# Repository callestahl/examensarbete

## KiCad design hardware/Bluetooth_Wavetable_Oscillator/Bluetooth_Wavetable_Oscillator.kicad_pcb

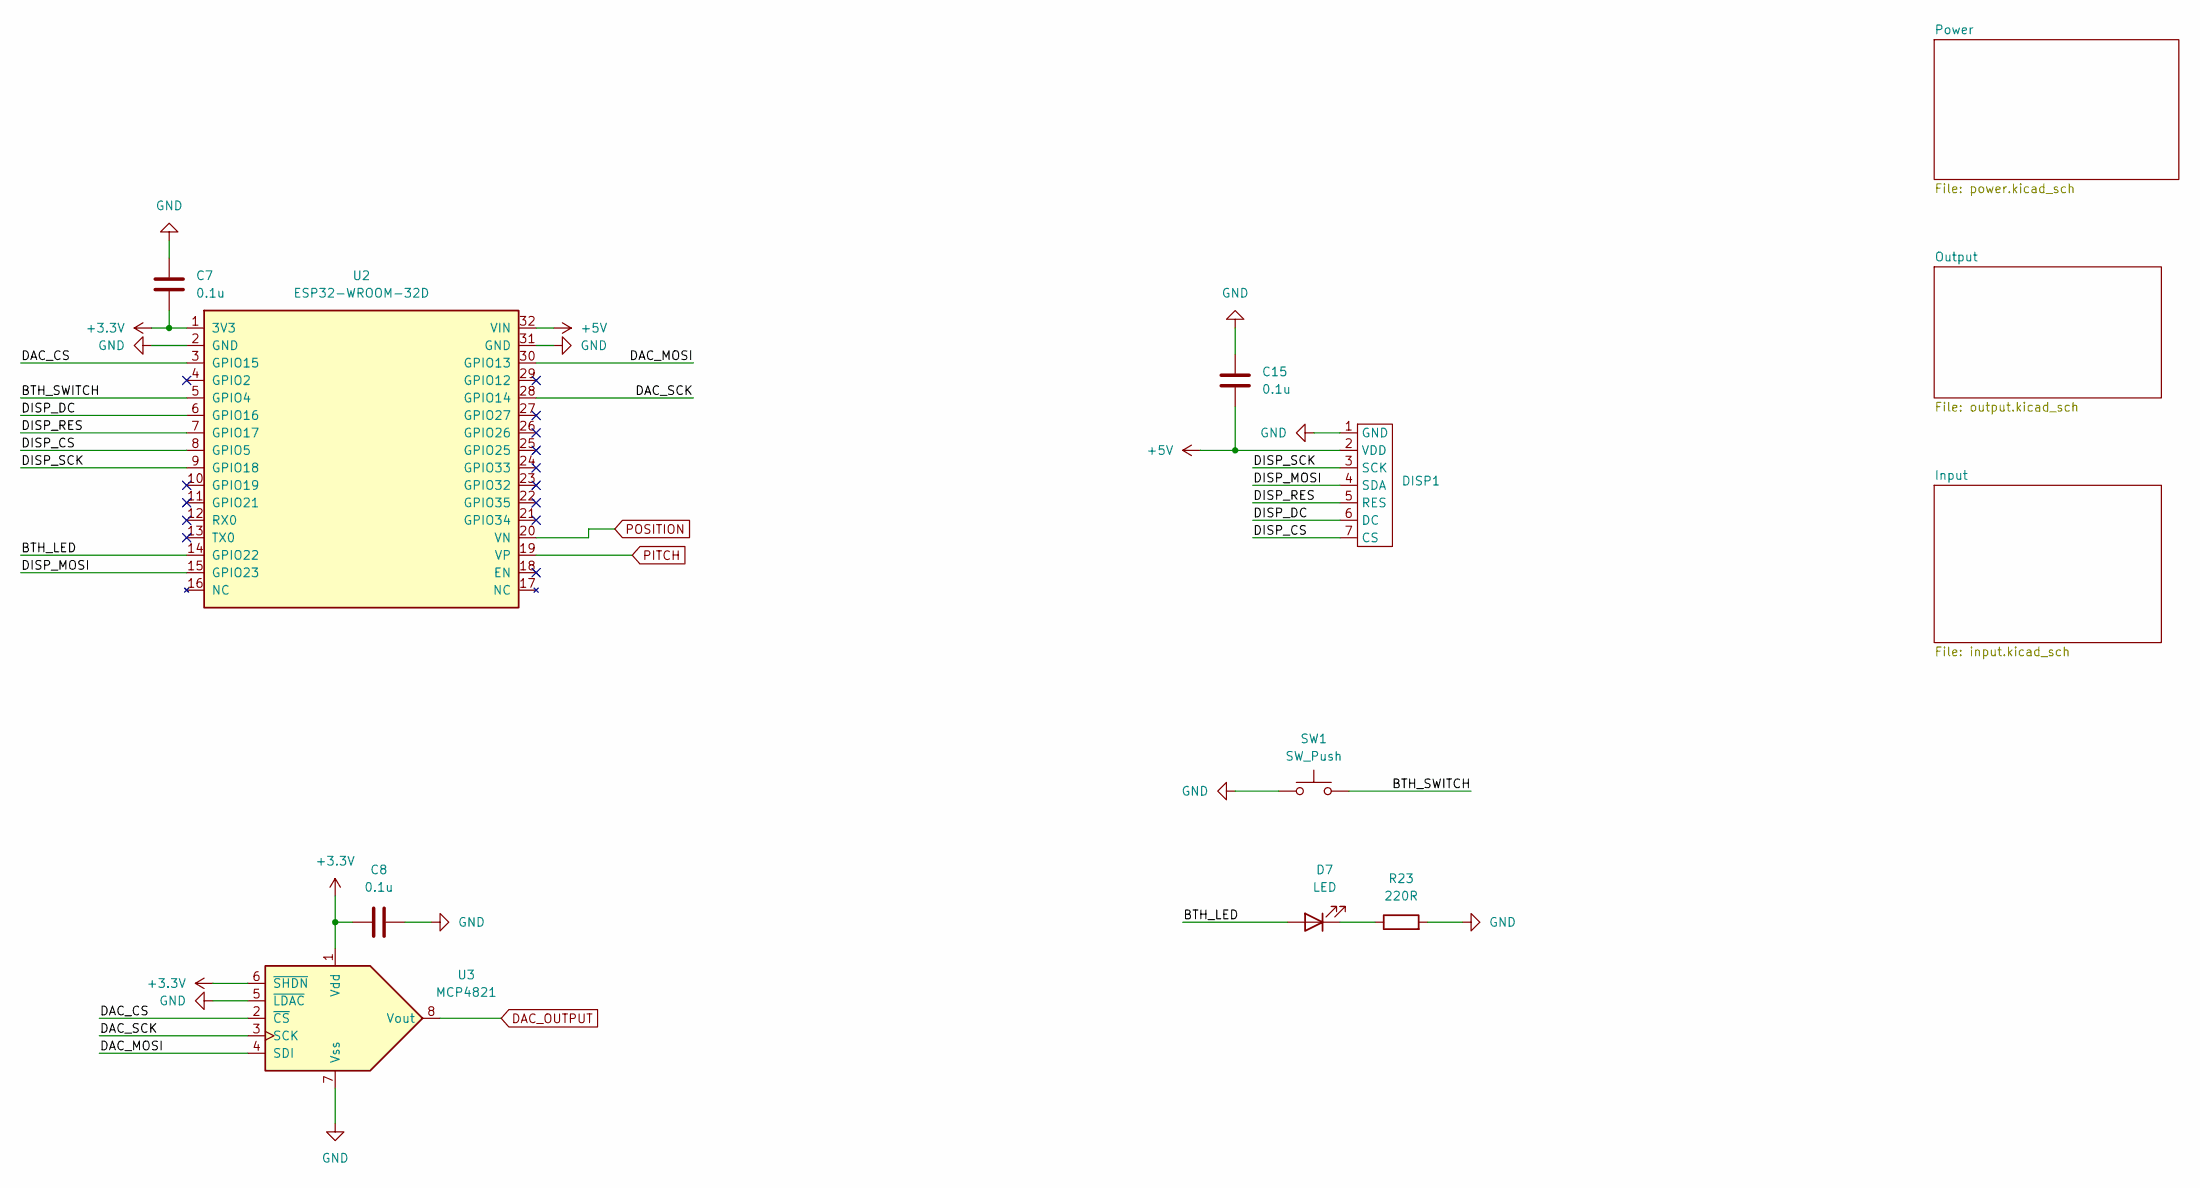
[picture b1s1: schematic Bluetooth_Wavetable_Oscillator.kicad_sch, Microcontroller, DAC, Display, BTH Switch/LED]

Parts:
C7, C8, C15: 0.1u; C_Disc_D5.0mm_W2.5mm_P5.00mm
D7: LED; D_A-405_P2.54mm_Vertical_AnodeUp
DISP1: 1.5inch_RGB_OLED_Module
R23: 220R; R_Axial_DIN0204_L3.6mm_D1.6mm_P2.54mm_Vertical
SW1: SW_Push; 6Pin-Switch-Button
U2: ESP32-WROOM-32D; ESP32
U3: MCP4821; DIP-8_W7.62mm

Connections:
+3.3V: C7.2, C8.1, U2.1 (3V3), U3.1 (Vdd), U3.6 (~SHDN); also elsewhere on the board
+5V: C15.2, DISP1.2 (VDD), U2.32 (VIN); also elsewhere on the board
/BTH_LED: D7.2 (A), U2.14 (GPIO22)
/BTH_SWITCH: SW1.2, U2.5 (GPIO4)
/DAC_CS: U2.3 (GPIO15), U3.2 (~CS)
/DAC_MOSI: U2.30 (GPIO13), U3.4 (SDI)
/DAC_SCK: U2.28 (GPIO14), U3.3 (SCK)
/DISP_CS: DISP1.7 (CS), U2.8 (GPIO5)
/DISP_DC: DISP1.6 (DC), U2.6 (GPIO16)
/DISP_MOSI: DISP1.4 (SDA), U2.15 (GPIO23)
/DISP_RES: DISP1.5 (RES), U2.7 (GPIO17)
/DISP_SCK: DISP1.3 (SCK), U2.9 (GPIO18)
DAC_OUTPUT: U3.8 (Vout); also elsewhere on the board
GND: C7.1, C8.2, C15.1, DISP1.1 (GND), R23.2, SW1.1, U2.2 (GND), U2.31 (GND), U3.5 (~LDAC), U3.7 (Vss); also elsewhere on the board
unnamed: D7.1 (K), R23.1
PITCH: U2.19 (VP); also elsewhere on the board
POSITION: U2.20 (VN); also elsewhere on the board

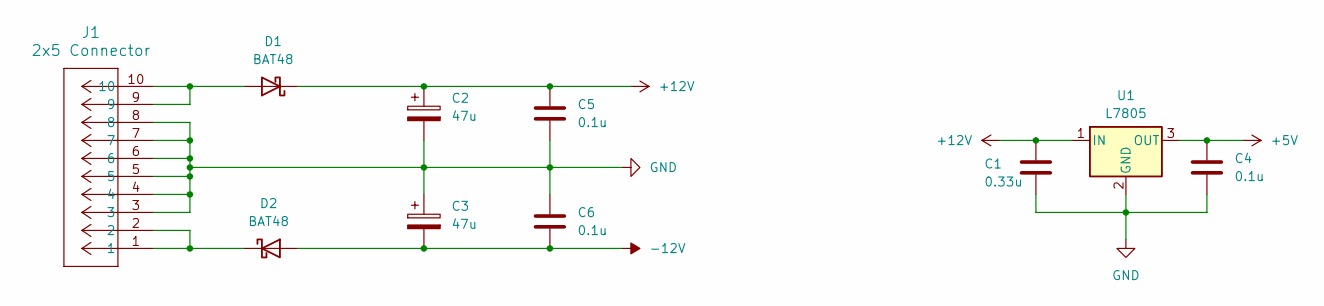
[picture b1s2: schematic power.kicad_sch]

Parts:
C1: 0.33u; C_Disc_D5.0mm_W2.5mm_P5.00mm
C2, C3: 47u; CP_Radial_D5.0mm_P2.50mm
C4, C5, C6: 0.1u; C_Disc_D5.0mm_W2.5mm_P5.00mm
D1, D2: BAT48; D_DO-35_SOD27_P2.54mm_Vertical_KathodeUp
J1: 2x5 Connector; 10_pin_eurorack_connector
U1: L7805; TO-220-3_Horizontal_TabDown

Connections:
+5V: C4.1, U1.3 (OUT); also elsewhere on the board
+12V: C1.1, C2.1, C5.1, D1.1 (K), U1.1 (IN); also elsewhere on the board
-12V: C3.2, C6.2, D2.2 (A); also elsewhere on the board
GND: C1.2, C2.2, C3.1, C4.2, C5.2, C6.1, J1.3, J1.4, J1.5, J1.6, J1.7, J1.8, U1.2 (GND); also elsewhere on the board
unnamed: D1.2 (A), J1.9, J1.10
unnamed: D2.1 (K), J1.1, J1.2

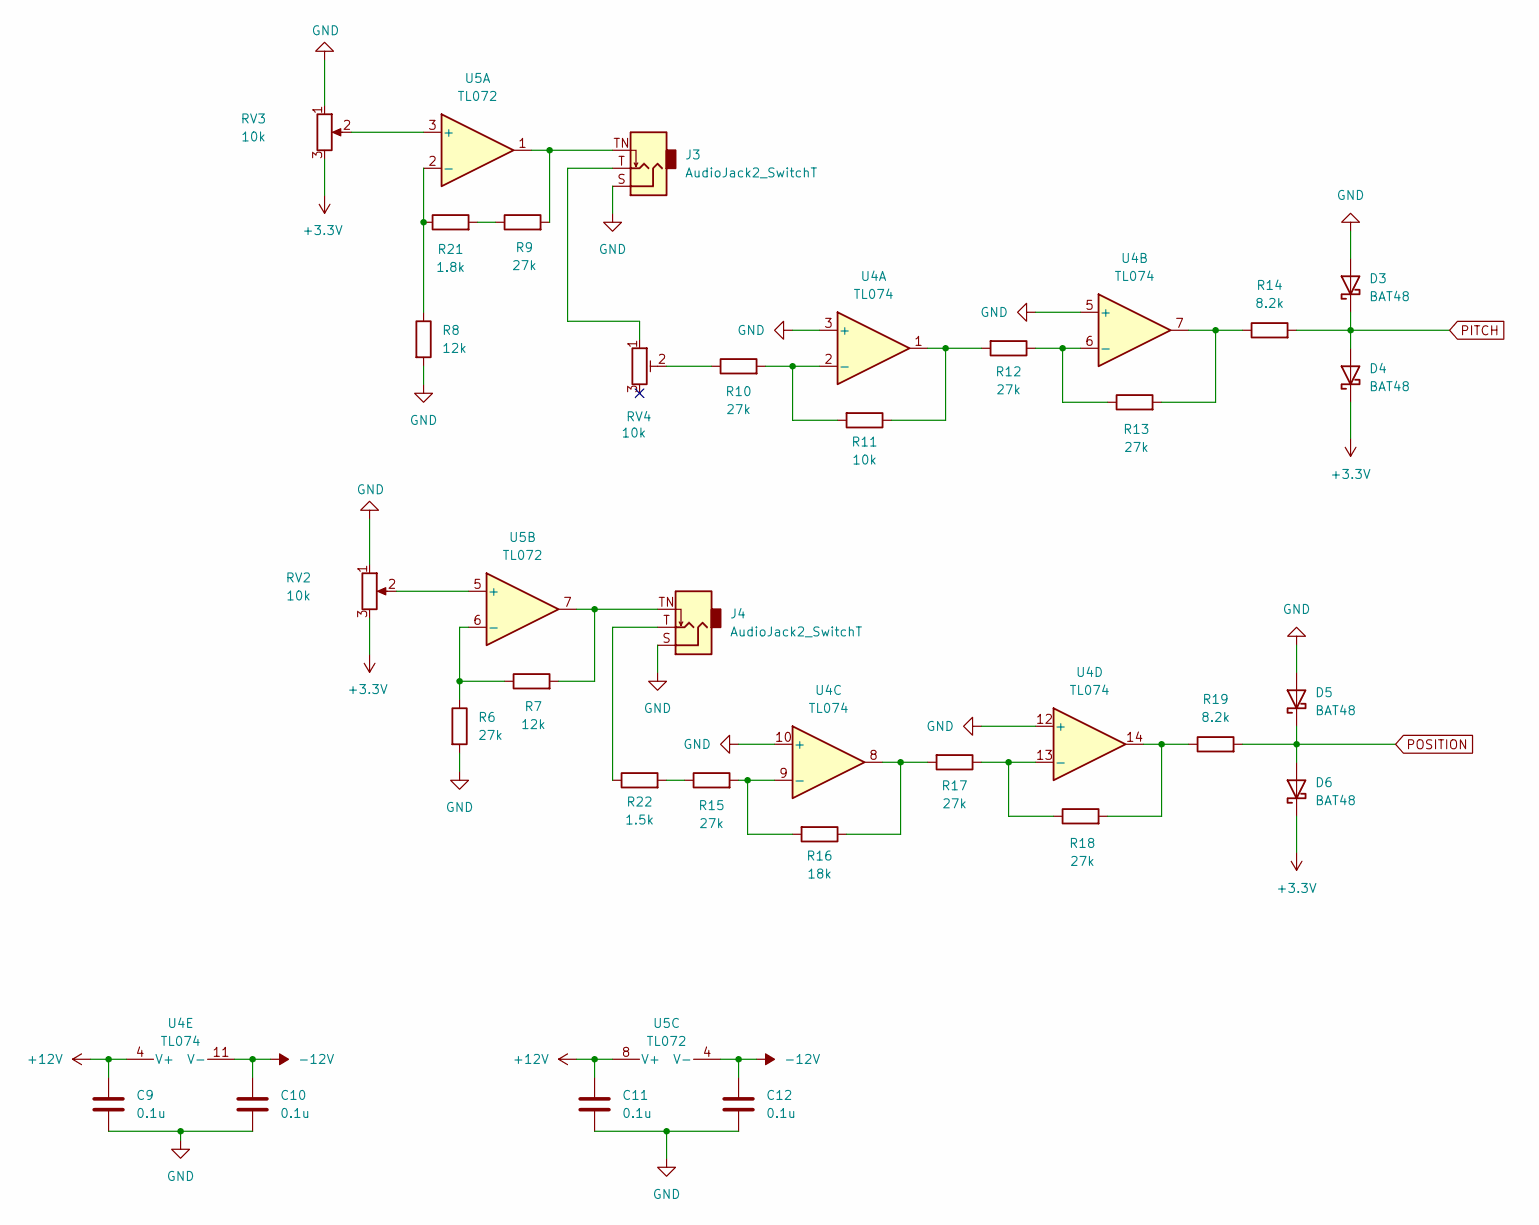
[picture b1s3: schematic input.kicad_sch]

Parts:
C9, C10, C11, C12: 0.1u; C_Disc_D5.0mm_W2.5mm_P5.00mm
D3, D4, D5, D6: BAT48; D_DO-34_SOD68_P7.62mm_Horizontal
J3, J4: AudioJack2_SwitchT; Jack_3.5mm_QingPu_WQP-PJ398SM_Vertical_CircularHoles
R6: 27k; R_Axial_DIN0204_L3.6mm_D1.6mm_P7.62mm_Horizontal
R7: 12k; R_Axial_DIN0204_L3.6mm_D1.6mm_P7.62mm_Horizontal
R8: 12k; R_Axial_DIN0204_L3.6mm_D1.6mm_P2.54mm_Vertical
R9, R10, R12, R13, R15, R17, R18: 27k; R_Axial_DIN0204_L3.6mm_D1.6mm_P2.54mm_Vertical
R11: 10k; R_Axial_DIN0204_L3.6mm_D1.6mm_P2.54mm_Vertical
R14, R19: 8.2k; R_Axial_DIN0204_L3.6mm_D1.6mm_P2.54mm_Vertical
R16: 18k; R_Axial_DIN0204_L3.6mm_D1.6mm_P2.54mm_Vertical
R21: 1.8k; R_Axial_DIN0204_L3.6mm_D1.6mm_P2.54mm_Vertical
R22: 1.5k; R_Axial_DIN0204_L3.6mm_D1.6mm_P2.54mm_Vertical
RV2, RV3: 10k; Potentiometer_Bourns_PTV09A-1_Single_Vertical
RV4: 10k; Trimmer-potentiometer
U4: TL074; DIP-14_W7.62mm
U5: TL072; DIP-8_W7.62mm

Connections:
+3.3V: D4.1 (K), D6.1 (K), RV2.3, RV3.3; also elsewhere on the board
+12V: C9.1, C11.1, U4.4 (V+), U5.8 (V+); also elsewhere on the board
-12V: C10.1, C12.1, U4.11 (V-), U5.4 (V-); also elsewhere on the board
GND: C9.2, C10.2, C11.2, C12.2, D3.2 (A), D5.2 (A), J3.S, J4.S, R6.2, R8.2, RV2.1, RV3.1, U4.3 (+), U4.5 (+), U4.10 (+), U4.12 (+); also elsewhere on the board
unnamed: J3.T, RV4.1
unnamed: J3.TN, R9.2, U5.1
unnamed: J4.T, R22.1
unnamed: J4.TN, R7.2, U5.7
unnamed: R10.1, RV4.2
unnamed: R11.1, R12.2, U4.1
unnamed: R13.2, R14.1, U4.7
unnamed: R15.1, R22.2
unnamed: R16.1, R17.2, U4.8
unnamed: R18.2, R19.1, U4.14
unnamed: R9.1, R21.2
unnamed: R10.2, R11.2, U4.2 (-)
unnamed: R12.1, R13.1, U4.6 (-)
unnamed: R15.2, R16.2, U4.9 (-)
unnamed: R17.1, R18.1, U4.13 (-)
unnamed: RV3.2, U5.3 (+)
unnamed: R8.1, R21.1, U5.2 (-)
unnamed: RV2.2, U5.5 (+)
unnamed: R6.1, R7.1, U5.6 (-)
PITCH: D3.1 (K), D4.2 (A), R14.2; also elsewhere on the board
POSITION: D5.1 (K), D6.2 (A), R19.2; also elsewhere on the board

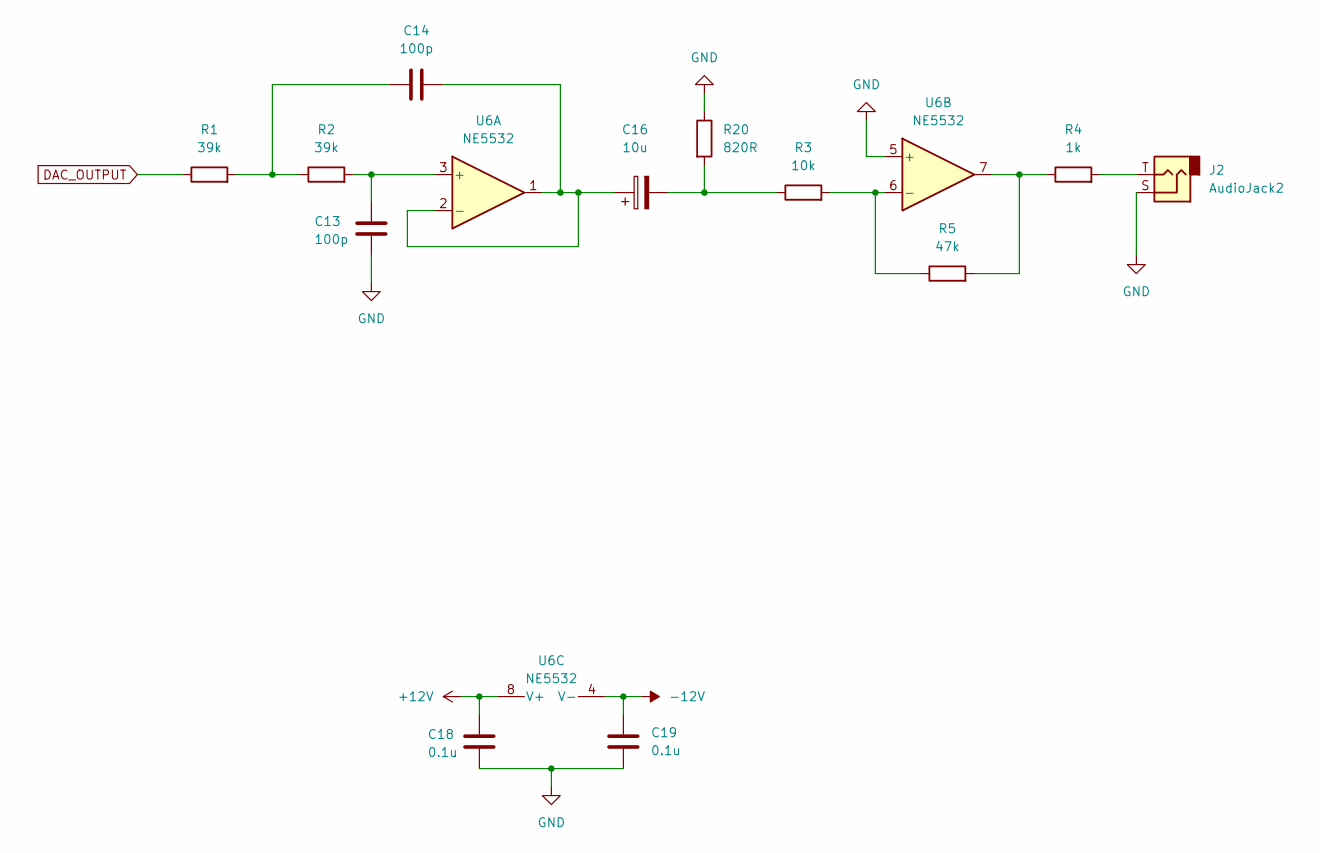
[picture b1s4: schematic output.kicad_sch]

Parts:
C13, C14: 100p; C_Disc_D5.0mm_W2.5mm_P5.00mm
C16: 10u; CP_Radial_D5.0mm_P2.50mm
C18, C19: 0.1u; C_Disc_D5.0mm_W2.5mm_P5.00mm
J2: AudioJack2; Jack_3.5mm_QingPu_WQP-PJ398SM_Vertical_CircularHoles
R1, R2: 39k; R_Axial_DIN0204_L3.6mm_D1.6mm_P7.62mm_Horizontal
R3: 10k; R_Axial_DIN0204_L3.6mm_D1.6mm_P7.62mm_Horizontal
R4: 1k; R_Axial_DIN0204_L3.6mm_D1.6mm_P7.62mm_Horizontal
R5: 47k; R_Axial_DIN0204_L3.6mm_D1.6mm_P7.62mm_Horizontal
R20: 820R; R_Axial_DIN0204_L3.6mm_D1.6mm_P7.62mm_Horizontal
U6: NE5532; DIP-8_W7.62mm

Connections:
+12V: C18.1, U6.8 (V+); also elsewhere on the board
-12V: C19.1, U6.4 (V-); also elsewhere on the board
DAC_OUTPUT: R1.1; also elsewhere on the board
GND: C13.2, C18.2, C19.2, J2.S, R20.1, U6.5 (+); also elsewhere on the board
unnamed: C14.2, R1.2, R2.1
unnamed: C16.2, R3.1, R20.2
unnamed: J2.T, R4.2
unnamed: R4.1, R5.2, U6.7
unnamed: C13.1, R2.2, U6.3 (+)
unnamed: C14.1, C16.1, U6.1, U6.2 (-)
unnamed: R3.2, R5.1, U6.6 (-)

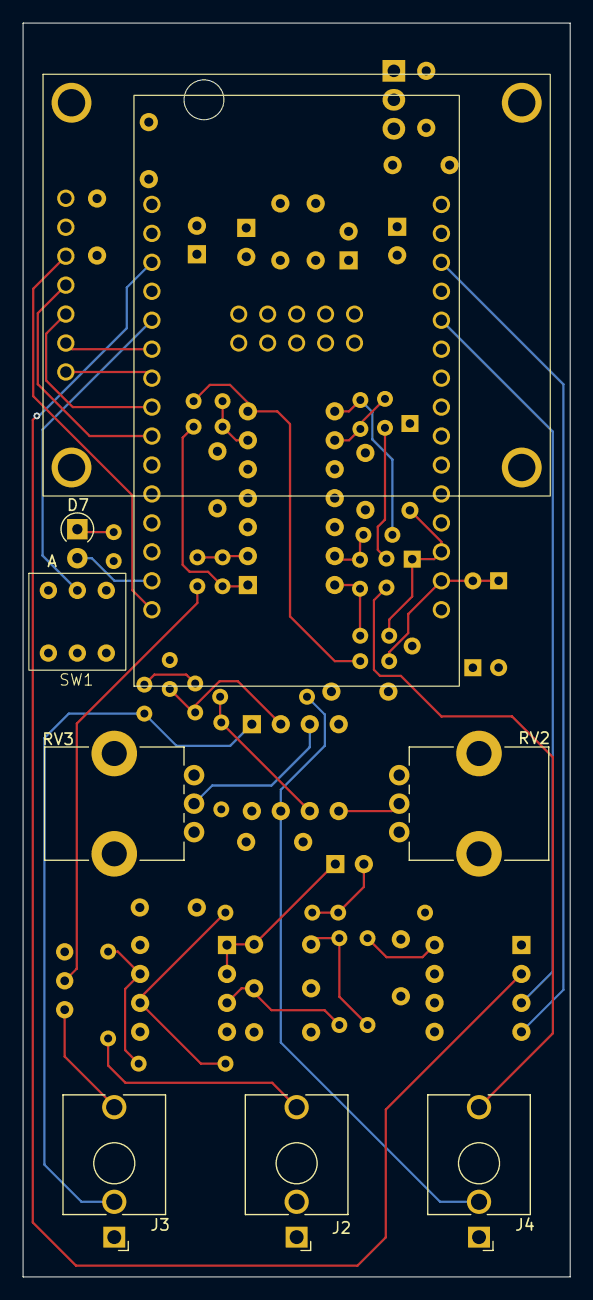
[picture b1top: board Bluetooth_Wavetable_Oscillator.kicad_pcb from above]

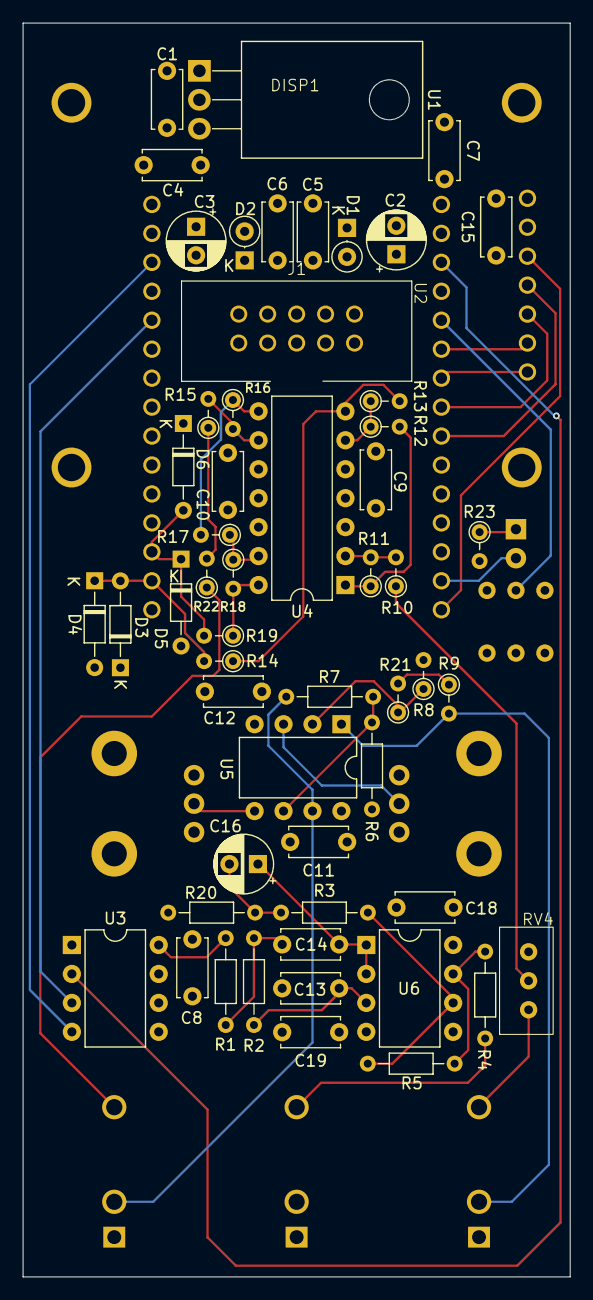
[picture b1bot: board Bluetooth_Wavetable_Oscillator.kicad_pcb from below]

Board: 4 copper layers, 48.0 x 110.0 mm, 63 parts (54 on the bottom side), 47 nets.

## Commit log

2024-11-06 first
2024-11-06 Ported code from pico to esp32
2024-11-07 add analog to pitch function
2024-11-07 Bluetooth and other display things
2024-11-07 Can send files over bluetooth from desktop
2024-11-07 Desktop ui touch ups
2024-11-08 Wav file reading
2024-11-08 normalize sound buffer
2024-11-08 New configurations
2024-11-08 More bluecove dependencies
2024-11-08 autocorrelation test
2024-11-08 Git is mad
2024-11-08 write averagesamples array to file
2024-11-08 Skuff impl, cycle sample count calculation
2024-11-09 Starting on sending over converted files, but badly
2024-11-09 Cycles to device bluetooth logic working
2024-11-10 slå ihop ino-filer
2024-11-10 fix forloop
2024-11-11 update first_pass
2024-11-11 Different files
2024-11-11 fungerande oscillator
2024-11-13 Added support for compiling, suggestions, and uploading on terminal
2024-11-13 More work on bluetooth, safety, reliability, data lost
2024-11-14 Refactoring of bluetooth logic
2024-11-14 More refactoring and bug fix
2024-11-14 add kicad project
2024-11-15 Java impl, alla files in one
2024-11-15 Task for drawing
2024-11-16 Starting on BLE implementation
2024-11-18 first schematic
2024-11-18 Ble impl done, spp bigger buffer sizes
2024-11-18 For presentation
2024-11-19 C impl for SPP
2024-11-20 Cpp implementation of the user interface
2024-11-20 BLE now works in c++
2024-11-20 Removed unecissary comments
2024-11-20 Moved different setup in different directories
2024-11-21 bluetooth logic in seperate task, mutex on oscillator writes, notify task to run
2024-11-22 New algoritm for changing cycle index
2024-11-22 comment out buggy algorithm
2024-11-22 Uppdated algo
2024-11-22 Think the cycle index logic works
2024-11-23 Changed the ble setup
2024-11-23 Save waveforms to file system
2024-11-24 Some profiling for testing
2024-11-25 add audio test files
2024-11-25 change ADC input pins in schematic
2024-11-25 New drawing logic
2024-11-26 add diagram scripts
2024-11-28 add bth components, add component values, update SPI pins, change disp power supply to 5V
2024-11-28 Bluetooth on by button click
2024-11-29 start PCB layout
2024-11-29 add kicad libraries
2024-12-02 update esp32 footprint
2024-12-02 BLE setup for testing
2024-12-02 update shematic, PCB and footprints
2024-12-09 all items connected
2024-12-09 fix silkscreen clipping
2024-12-09 passing DRC
2024-12-12 Test results
2024-12-15 changing test files
2024-12-17 For other tests
2024-12-28 add Effekt
2025-01-02 add feedback capacitor
2025-01-03 add scematic PDF
2025-01-03 add schematic pngs
2025-01-04 Some changes for cleanup
2025-01-04 More cleanup
2025-01-09 Clean up of repository
2025-01-09 Create LICENSE
2025-01-09 Removed submodule to reinstall it later
2025-01-09 Added the submodule back
2025-01-10 Looking for adresses on a seperate thread on SPP for faster startup
2025-01-19 Some cleanup
2025-01-19 Removed chache
